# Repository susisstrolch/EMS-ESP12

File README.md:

# EMS-ESP8266/12
EMS Gateway with ESP8266/ESP-12 module

Wireless "Buderus EMS-Bus" interface for "collectord".

For Eagle schematics see https://github.com/susisstrolch/EMS-ESP8266_12-PCB

code parts based/derived from
- Espressif ESP8266 SDK (ESP_IOS_SDK V0.95 - 15.01.2015)
  http://bbs.espressif.com/viewtopic.php?f=5&t=154

- beckdac's "Transparent Bridge for ESP8266"
  https://github.com/beckdac/ESP8266-transparent-bridge
	
- ethersex by Danny Baumann
  https://github.com/maniac103/ethersex

Additional links
  Logamatic 2107 Schnittstelle   - http://www.mikrocontroller.net/topic/141831#new
  Buderus EMS Gateway mit PIC18F - http://www.mikrocontroller.net/topic/210031#new
  Faktensammlung Buderus EMS     - http://www.mikrocontroller.net/topic/309075#new
  EMS > Adapter > NetIO > Raspi  - http://www.mikrocontroller.net/topic/318364#new
  Ingo F's EMS-Gateway WIKI      - http://ems-gateway.myds.me/dokuwiki/doku.php

  ESP8266 Community Forum        - http://www.esp8266.com
  Espressif Board Forum          - http://bbs.espressif.com

  Dirt Cheap Dirty Boards        - http://dirtypcbs.com/

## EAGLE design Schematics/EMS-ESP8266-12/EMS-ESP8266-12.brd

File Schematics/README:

Eagle Design Files for EMS-ESP12 interface

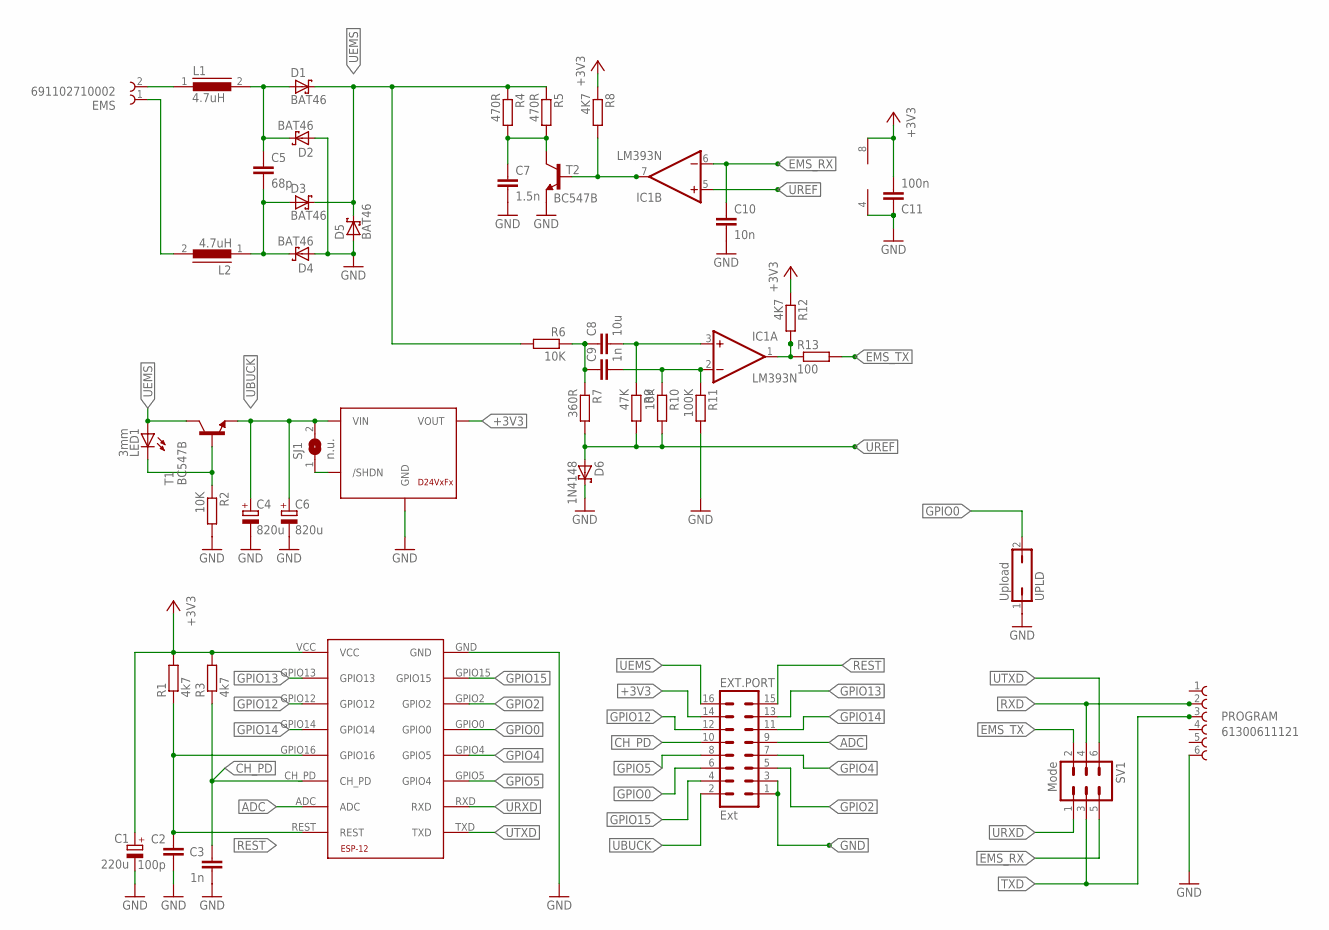
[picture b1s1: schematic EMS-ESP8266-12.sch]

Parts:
C1: 220u; UD-6,3X5,8_NICHICON
C2: 100p; C2.5-2
C3, C9: 1n; C2.5-2
C4, C6: 820u; UD-10X10_NICHICON
C5: 68p; C025-050X050
C7: 1.5n; C2.5-2
C8: 10u; C5B11
C10: 10n; C2.5-2
C11: 100n; C2.5-2
D1, D2, D3, D4, D5: BAT46; DO35-7
D6: 1N4148; DO35-7
EMS: 691102710002
ESP1: ESP-12ESP-12; ESP-12
EXT.PORT: Ext; MA08-2
IC1: LM393N; DIL08
L1, L2: 4.7uH; MICC12
LED1: 3mm; LED3MM
MOD1: D24V3F3; D24VXFX
PROGRAM: 61300611121
R1, R3: 4k7; 0204/7
R2, R6, R10: 10K; 0204/7
R4, R5: 470R; 0204/7
R7: 360R; 0204/7
R8, R12: 4K7; 0204/7
R9: 47K; 0204/7
R11: 100K; 0204/7
R13: 100; 0204/7
SJ1: n.u.; SJ
SV1: Mode; MA03-2
T1, T2: BC547B; TO92-EBC
UPLD: Upload; JP1

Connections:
+3V3: C1.+, C11.2, ESP1.VCC, EXT.PORT.14, IC1.8 (V+), MOD1.VOUT, R1.2, R3.2, R8.1, R12.1
ADC: ESP1.ADC, EXT.PORT.9
CH_PD: C3.1, ESP1.CH_PD, EXT.PORT.10, R3.1
EMS_RX: C10.1, IC1.6 (-IN), SV1.5
EMS_TX: R13.2, SV1.2
GND: C1.-, C2.2, C3.2, C4.-, C6.-, C7.2, C10.2, C11.1, D2.A, D4.A, D5.A, D6.C, ESP1.GND, EXT.PORT.1, EXT.PORT.3, IC1.4 (V-), MOD1.GND, PROGRAM.6, R2.2, R11.2, T2.E, UPLD.1
GPIO0: ESP1.GPIO0, EXT.PORT.6, UPLD.2
GPIO2: ESP1.GPIO2, EXT.PORT.5
GPIO4: ESP1.GPIO4 (GPIO5), EXT.PORT.7
GPIO5: ESP1.GPIO5 (GPIO4), EXT.PORT.8
GPIO12: ESP1.GPIO12, EXT.PORT.12
GPIO13: ESP1.GPIO13, EXT.PORT.13
GPIO14: ESP1.GPIO14, EXT.PORT.11
GPIO15: ESP1.GPIO15, EXT.PORT.4
unnamed: C5.1, D1.A, D2.C, L1.2
unnamed: C5.2, D3.A, D4.C, L2.1
unnamed: MOD1./SHDN, SJ1.1
unnamed: EMS.2, L1.1
unnamed: IC1.1 (OUT), R12.2, R13.1
unnamed: C7.1, R4.2, R5.2, T2.C
unnamed: C8.1, C9.1, R6.1, R7.1
unnamed: EMS.1, L2.2
unnamed: C8.2, IC1.3 (+IN), R9.1
unnamed: C9.2, IC1.2 (-IN), R10.1, R11.1
unnamed: IC1.7 (OUT), R8.2, T2.B
unnamed: LED1.K (C), R2.1, T1.B
REST: C2.1, ESP1.GPIO16, ESP1.REST, EXT.PORT.15, R1.1
RXD: PROGRAM.2, SV1.4
TXD: PROGRAM.3, SV1.3
UBUCK: C4.+, C6.+, EXT.PORT.2, MOD1.VIN, SJ1.2, T1.E
UEMS: D1.C, D3.C, D5.C, EXT.PORT.16, LED1.A, R4.1, R5.1, R6.2, T1.C
UREF: D6.A, IC1.5 (+IN), R7.2, R9.2, R10.2
URXD: ESP1.RXD, SV1.1
UTXD: ESP1.TXD, SV1.6

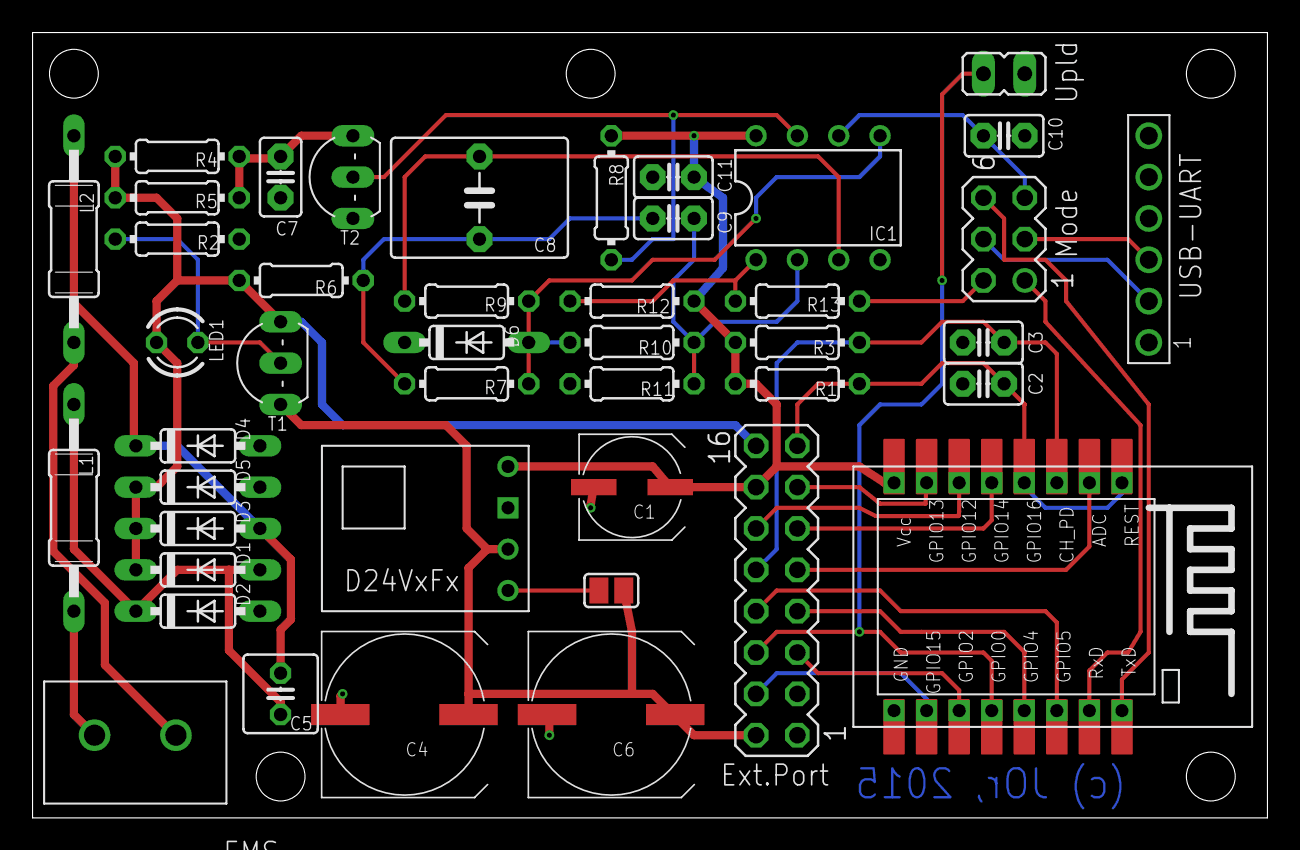
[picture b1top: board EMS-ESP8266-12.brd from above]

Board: 2 copper layers, 75.9 x 48.2 mm, 44 parts (0 on the bottom side), 34 nets.

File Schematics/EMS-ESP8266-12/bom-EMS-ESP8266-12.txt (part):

Partlist exported from /home/jorschiedt/Development/Heizung/EMS-ESP12/Schematics/EMS-ESP8266-12/EMS-ESP8266-12.sch at 2/8/15 2:24 PM

Part     Value        Device               Package             Description                                                                                                                                   CONRAD         MF MPN OC_FARNELL OC_NEWARK
C1       220u         CPOL-EUUD-6,3X8,8    UD-6,3X5,8_NICHICON POLARIZED CAPACITOR, European symbol                                                                                                          VF 220/6,3 P-D                            
C2       100p         C2.5/2               C2.5-2              CAPACITOR                                                                                                                                                                               
C3       1n           C2.5/2               C2.5-2              CAPACITOR                                                                                                                                                                               
C4       820u         CPOL-EUUD-10X10      UD-10X10_NICHICON   POLARIZED CAPACITOR, European symbol                                                                                                          VF 820/16 P-G                             
C5       68p          C-EU025-050X050      C025-050X050        CAPACITOR, European symbol                                                                                                                    457221-62                                 
C6       820u         CPOL-EUUD-10X10      UD-10X10_NICHICON   POLARIZED CAPACITOR, European symbol                                                                                                          VF 820/16 P-G                             
C7       1.5n         C2.5/2               C2.5-2              CAPACITOR                                                                                                                                                                               
C8       10u          C5/11                C5B11               CAPACITOR                                                                                                                                     450662-62                                 
C9       1n           C2.5/2               C2.5-2              CAPACITOR                                                                                                                                     453005-62                                 
C10      10n          C2.5/2               C2.5-2              CAPACITOR                                                                                                                                                                               
C11      100n         C2.5/2               C2.5-2              CAPACITOR                                                                                                                                                                               
D1       BAT46        SCHOTTKY-DIODEDO35-7 DO35-7              Schottky Diode                                                                                                                                153087-62                                 
D2       BAT46        SCHOTTKY-DIODEDO35-7 DO35-7              Schottky Diode                                                                                                                                153087-62                                 
D3       BAT46        SCHOTTKY-DIODEDO35-7 DO35-7              Schottky Diode                                                                                                                                153087-62                                 
D4       BAT46        SCHOTTKY-DIODEDO35-7 DO35-7              Schottky Diode                                                                                                                                153087-62                                 
D5       BAT46        SCHOTTKY-DIODEDO35-7 DO35-7              Schottky Diode                                                                                                                                153087-62                                 
D6       1N4148       SCHOTTKY-DIODEDO35-7 DO35-7              Schottky Diode                                                                                                                                162280-62                                 
EMS      691102710002 691102710002         691102710002        WR-TBL Serie 102 - 5.0mm Horizontal Entry Modular with Pressure Clamp - 1.5mm2 Wires, 2 Pins=>Code : Con_TBL_Screw_PressureClamp_691102710002                                           
ESP1     ESP-12ESP-12 ESP-12ESP-12         ESP-12              low cost Wifi to Serial Module                                                                                                                                                          
EXT.PORT Ext          MA08-2               MA08-2              PIN HEADER                                                                                                                                                          unknown    unknown  
IC1      LM393N       LM393N               DIL08               COMPARATOR                                                                                                                                                                              
L1       4.7uH        MICC12               MICC12              INDUCTOR                                                                                                                                      440391-62                                 
L2       4.7uH        MICC12               MICC12              INDUCTOR                                                                                                                                      440391-62                                 
LED1     3mm          LED3MM               LED3MM              LED                                                                                                                                                                                     
MOD1     D24V3F3      D24VXFX              D24VXFX             Step-Down Spannungsregler                                                                                                                                                               
PROGRAM  61300611121  61300611121          61300611121         WR-PHD 2.54mm Pin Header, 6 Pin =>Code : Con_BTB_PHD_2.54_1_THT_61300611121                                                                                                             
R1       4k7          R-EU_0204/7          0204/7              RESISTOR, European symbol                                                                                                                                                               
R2       10K          R-EU_0204/7          0204/7              RESISTOR, European symbol                                                                                                                                                               
R3       4k7          R-EU_0204/7          0204/7              RESISTOR, European symbol                                                                                                                                                               
R4       470R         R-EU_0204/7          0204/7              RESISTOR, European symbol                                                                                                                                                               
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
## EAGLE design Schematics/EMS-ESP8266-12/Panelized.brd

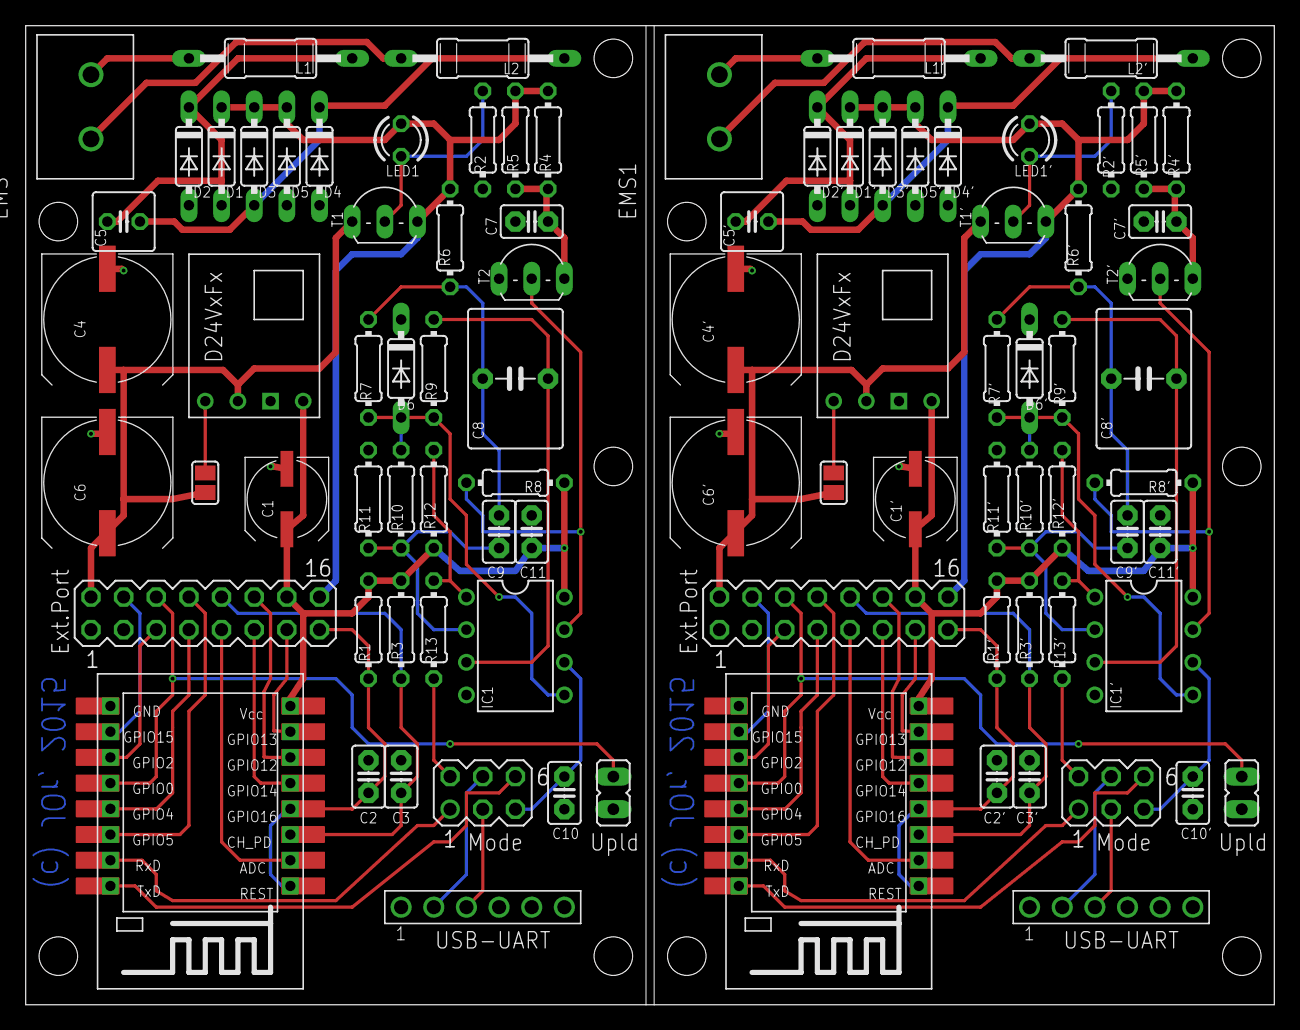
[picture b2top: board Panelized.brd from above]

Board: 2 copper layers, 97.1 x 76.2 mm, 88 parts (0 on the bottom side), 68 nets.

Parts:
C1, C1': 220u; UD-6,3X5,8_NICHICON
C2, C2': 100p; C2.5-2
C3, C3', C9, C9': 1n; C2.5-2
C4, C4', C6, C6': 820u; UD-10X10_NICHICON
C5, C5': 68p; C025-050X050
C7, C7': 1.5n; C2.5-2
C8, C8': 10u; C5B11
C10, C10': 10n; C2.5-2
C11, C11': 100n; C2.5-2
D1, D1', D2, D2', D3, D3', D4, D4', D5, D5': BAT46; DO35-7
D6, D6': 1N4148; DO35-7
EMS, EMS1: 691102710002
ESP1, ESP2: ESP-12ESP-12; ESP-12
EXT.PORT, EXT.PORT1: Ext; MA08-2
IC1, IC1': LM393N; DIL08
L1, L1', L2, L2': 4.7uH; MICC12
LED1, LED1': 3mm; LED3MM
MOD1, MOD2: D24V3F3; D24VXFX
PROGRAM, PROGRAM1: 61300611121
R1, R1', R3, R3': 4k7; 0204/7
R2, R2', R6, R6', R10, R10': 10K; 0204/7
R4, R4', R5, R5': 470R; 0204/7
R7, R7': 360R; 0204/7
R8, R8', R12, R12': 4K7; 0204/7
R9, R9': 47K; 0204/7
R11, R11': 100K; 0204/7
R13, R13': 100; 0204/7
SJ1, SJ2: n.u.; SJ
SV1, SV2: Mode; MA03-2
T1, T1', T2, T2': BC547B; TO92-EBC
UPLD, UPLD1: Upload; JP1

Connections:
+3V1: C1'.+, C11'.2, ESP2.VCC, EXT.PORT1.14, IC1'.8, MOD2.VOUT, R1'.2, R3'.2, R8'.1, R12'.1
+3V3: C1.+, C11.2, ESP1.VCC, EXT.PORT.14, IC1.8, MOD1.VOUT, R1.2, R3.2, R8.1, R12.1
ADC: ESP1.ADC, EXT.PORT.9
ADC1: ESP2.ADC, EXT.PORT1.9
CH_PD: C3.1, ESP1.CH_PD, EXT.PORT.10, R3.1
CH_PD1: C3'.1, ESP2.CH_PD, EXT.PORT1.10, R3'.1
EMS_RX: C10.1, IC1.6, SV1.5
EMS_RX1: C10'.1, IC1'.6, SV2.5
EMS_TX: R13.2, SV1.2
EMS_TX1: R13'.2, SV2.2
GND: C1.-, C2.2, C3.2, C4.-, C6.-, C7.2, C10.2, C11.1, D2.A, D4.A, D5.A, D6.C, ESP1.GND, EXT.PORT.1, EXT.PORT.3, IC1.4, MOD1.GND, PROGRAM.6, R2.2, R11.2, T2.E, UPLD.1
GND1: C1'.-, C2'.2, C3'.2, C4'.-, C6'.-, C7'.2, C10'.2, C11'.1, D2'.A, D4'.A, D5'.A, D6'.C, ESP2.GND, EXT.PORT1.1, EXT.PORT1.3, IC1'.4, MOD2.GND, PROGRAM1.6, R2'.2, R11'.2, T2'.E, UPLD1.1
GPIO0: ESP1.GPIO0, EXT.PORT.6, UPLD.2
GPIO1: ESP2.GPIO2, EXT.PORT1.5
GPIO2: ESP1.GPIO2, EXT.PORT.5
GPIO3: ESP2.GPIO4, EXT.PORT1.7
GPIO4: ESP1.GPIO4, EXT.PORT.7
GPIO5: ESP1.GPIO5, EXT.PORT.8
GPIO6: ESP2.GPIO13, EXT.PORT1.13
GPIO7: ESP2.GPIO12, EXT.PORT1.12
GPIO8: ESP2.GPIO14, EXT.PORT1.11
GPIO9: ESP2.GPIO0, EXT.PORT1.6, UPLD1.2
GPIO10: ESP2.GPIO5, EXT.PORT1.8
GPIO11: ESP2.GPIO15, EXT.PORT1.4
GPIO12: ESP1.GPIO12, EXT.PORT.12
GPIO13: ESP1.GPIO13, EXT.PORT.13
GPIO14: ESP1.GPIO14, EXT.PORT.11
GPIO15: ESP1.GPIO15, EXT.PORT.4
unnamed: C5.1, D1.A, D2.C, L1.2
unnamed: C5.2, D3.A, D4.C, L2.1
unnamed: MOD1./SHDN, SJ1.1
unnamed: EMS.2, L1.1
unnamed: IC1.1, R12.2, R13.1
unnamed: C7.1, R4.2, R5.2, T2.C
unnamed: C8.1, C9.1, R6.1, R7.1
unnamed: EMS.1, L2.2
unnamed: C8.2, IC1.3, R9.1
unnamed: C5'.2, D3'.A, D4'.C, L2'.1
unnamed: C8'.1, C9'.1, R6'.1, R7'.1
unnamed: C9.2, IC1.2, R10.1, R11.1
unnamed: C5'.1, D1'.A, D2'.C, L1'.2
unnamed: C9'.2, IC1'.2, R10'.1, R11'.1
unnamed: IC1.7, R8.2, T2.B
unnamed: IC1'.1, R12'.2, R13'.1
unnamed: LED1.K, R2.1, T1.B
unnamed: IC1'.7, R8'.2, T2'.B
unnamed: C7'.1, R4'.2, R5'.2, T2'.C
unnamed: C8'.2, IC1'.3, R9'.1
unnamed: LED1'.K, R2'.1, T1'.B
unnamed: EMS1.1, L2'.2
unnamed: EMS1.2, L1'.1
unnamed: MOD2./SHDN, SJ2.1
REST: C2.1, ESP1.GPIO16, ESP1.REST, EXT.PORT.15, R1.1
REST1: C2'.1, ESP2.GPIO16, ESP2.REST, EXT.PORT1.15, R1'.1
RXD: PROGRAM.2, SV1.4
RXD1: PROGRAM1.2, SV2.4
TXD: PROGRAM.3, SV1.3
TXD1: PROGRAM1.3, SV2.3
UBUCK: C4.+, C6.+, EXT.PORT.2, MOD1.VIN, SJ1.2, T1.E
UBUCK1: C4'.+, C6'.+, EXT.PORT1.2, MOD2.VIN, SJ2.2, T1'.E
UEMS: D1.C, D3.C, D5.C, EXT.PORT.16, LED1.A, R4.1, R5.1, R6.2, T1.C
UEMS1: D1'.C, D3'.C, D5'.C, EXT.PORT1.16, LED1'.A, R4'.1, R5'.1, R6'.2, T1'.C
UREF: D6.A, IC1.5, R7.2, R9.2, R10.2
UREF1: D6'.A, IC1'.5, R7'.2, R9'.2, R10'.2
URXD: ESP1.RXD, SV1.1
URXD1: ESP2.RXD, SV2.1
UTXD: ESP1.TXD, SV1.6
UTXD1: ESP2.TXD, SV2.6

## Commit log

2015-01-23 create small README, folder for EAGLE schematics
2015-01-24 add eagle design files add basic driver/user modules
2015-01-24 PCB reworked ° remove ground layer below ESP12-antenna ° change connector footprint ° 2pin debug connector ° small form factor for EMS connector
2015-01-27 Redesign - Board Rev. 1.0 - Debug Tx Anschluß entfällt, da bereits auf Ext. Port (GPIO2) - CH_PD auf Ext. Port geführt - Längsregler mit LED anstelle 3er Dioden. Als Seiteneffekt gibts eine Betriebsa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
2015-01-28 ESP8266/12 - Rev 1.0 - panelized for DirtyPCB - add descriptive Text to Layout and Headers / Jumpers
2015-01-28 ESP8266/12: add MS-panel.brd
2015-01-28 Board Rev 1.0b - Ext. Port auf 16pin erweitert - GPIO15 auf Ext. Port gelegt - erfordert im Normalbetrieb einen Jumper zw. Ext.Port, Pin 3-4 - Dummy Solder Jumper für Buck-Konverter /SHDN
2015-01-28 - add panelized Board for Rev 1.0b
2015-01-30 initial checkin for ems related files
2015-02-03 cleaning...
2015-02-03 still evolving....
2015-02-09 work in progress
2015-03-03 Attributes: add REICHELT order number and ALTERNATE package/part
2015-03-03 Additional CAM and DRU files
    CAM and DRU files for various board fabs (Seed, DirtyPCBs etc)
    BOK (bill of material)
2015-03-03 remove unused SNTP code
2015-03-04 app: add code for ntp and env
    ntp client: https://github.com/shantanugoel/esp8266-smartwatch
    env handling: https://github.com/nekromant/esp8266-frankenstein
2015-03-04 replace borked ntp.?, env.?
2015-04-21 checkin local work
2015-04-21 - add pictures to Schematics folder
2015-04-21 - add "empty" document to keep Rabbit happy..
2015-08-05 Cleanup: moved schematics to #EMS-ESP8266_12-PCB
2015-08-05 add PCB URL to README.md

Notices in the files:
parts and their libraries:
EagleLibrary_Wuerth_Elektronik_eiCan_Ter: Copyright: WÃÂÃÂÃÂÃÂ¼rth Elektronik
EagleLibrary_Wuerth_Elektronik_eiCan_Ter: Copyright: Würth Elektronik
